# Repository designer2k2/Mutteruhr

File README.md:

# Mutteruhr
a pulse of alternating polarity every minute.

Motherclock, or german "Mutteruhr" is a arduino based Master Clock or german "Hauptuhr". 
It generates a short pulse of alternating polarity to drive so called slave clocks or german "Nebenuhr".

https://en.wikipedia.org/wiki/Master_clock

With a DC/DC converter it uses minimal power, the highly accurate DS3231 RTC to keep time, and a Arduino Nano Every as a Brain.

## Circuit

Schematic: https://github.com/designer2k2/Mutteruhr/blob/main/MotherClock/Motherclock%20Schematic.pdf

The actual clock drive is a transistor h-bridge, parts can be either SMD or THT. 

2 Buttons and a DIL switch is on it to make settings while the clock operates.

A small mosfet can be used to switch some LED´s on/off

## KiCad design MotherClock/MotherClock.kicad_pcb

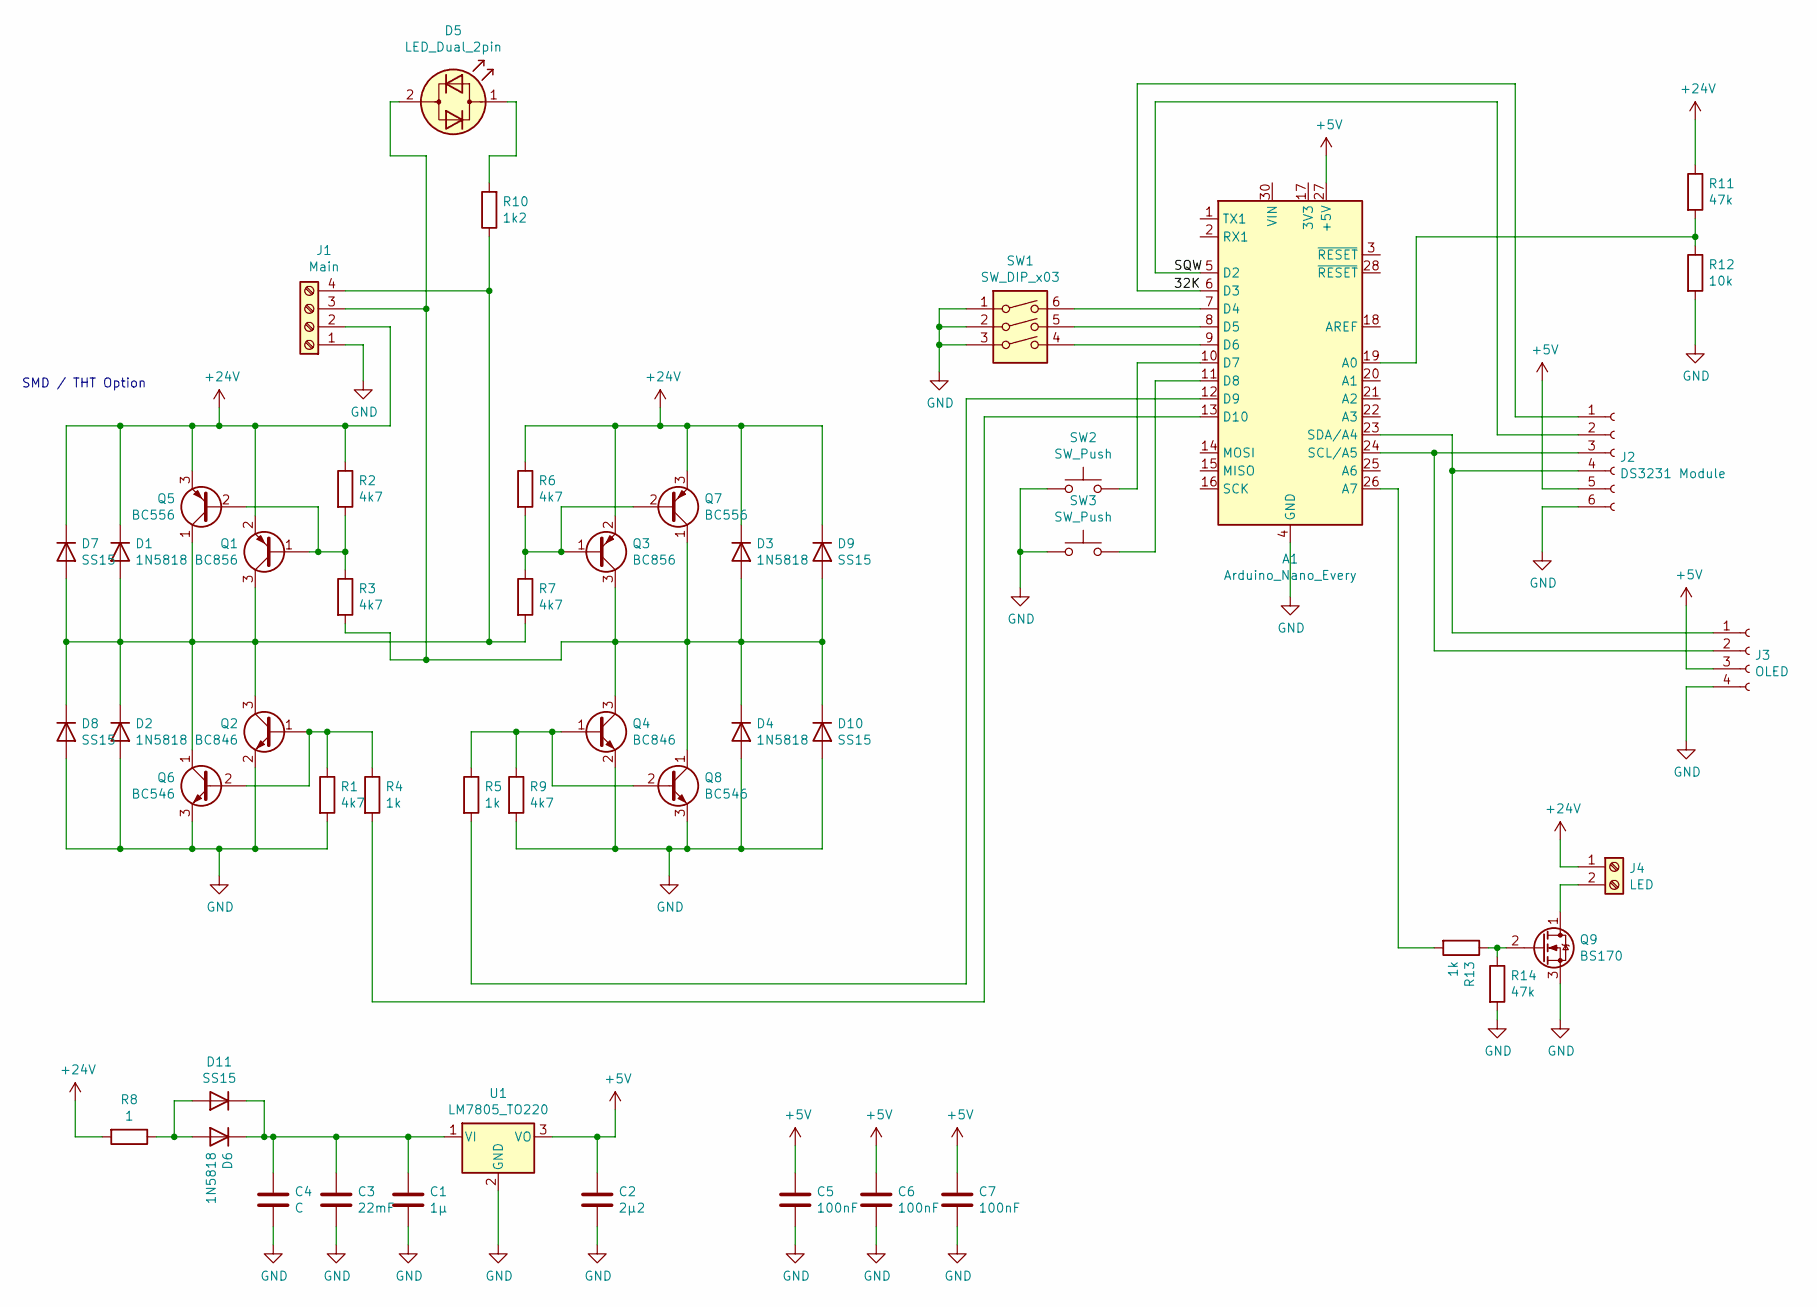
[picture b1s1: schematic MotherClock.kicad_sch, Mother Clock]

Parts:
A1: Arduino_Nano_Every; Arduino_Nano
C1: 1µ; CP_Radial_D5.0mm_P2.00mm
C2: 2µ2; CP_Radial_D5.0mm_P2.00mm
C3: 22mF; CP_Radial_D35.0mm_P10.00mm_SnapIn
C4: C; CP_Radial_D18.0mm_P7.50mm
C5, C6, C7: 100nF; C_0805_2012Metric
D1, D2, D3, D4, D6: 1N5818; D_DO-41_SOD81_P10.16mm_Horizontal
D5: LED_Dual_2pin; LED_D3.0mm_Clear
D7, D8, D9, D10, D11: SS15; D_SMA
J1: Main; TerminalBlock_Altech_AK300-4_P5.00mm
J2: DS3231 Module; PinHeader_1x06_P2.54mm_Vertical
J3: OLED; PinHeader_1x04_P2.54mm_Vertical
J4: LED; TerminalBlock_Altech_AK300-2_P5.00mm
Q1, Q3: BC856; SOT-23
Q2, Q4: BC846; SOT-23
Q5, Q7: BC556; TO-92_Inline_Wide
Q6, Q8: BC546; TO-92_Inline_Wide
Q9: BS170; TO-92_Inline
R1, R2, R3, R6, R7, R9: 4k7; R_1206_3216Metric
R4, R5, R13: 1k; R_1206_3216Metric
R8: 1; R_1206_3216Metric
R10: 1k2; R_1206_3216Metric
R11, R14: 47k; R_1206_3216Metric
R12: 10k; R_1206_3216Metric
SW1: SW_DIP_x03; SW_DIP_SPSTx03_Slide_9.78x9.8mm_W7.62mm_P2.54mm
SW2, SW3: SW_Push; SW_PUSH_6mm_H5mm
U1: LM7805_TO220; TO-220-3_Vertical

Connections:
+5V: A1.27 (+5V), C2.1, C5.1, C6.1, C7.1, J2.5, J3.3, U1.3 (VO)
+24V: D1.1 (K), D3.1 (K), D7.1 (K), D9.1 (K), J1.2, J4.1, Q1.2 (E), Q3.2 (E), Q5.3 (E), Q7.3 (E), R2.1, R6.1, R8.2, R11.1
GND: A1.4 (GND), A1.29 (GND), C1.2, C2.2, C3.2, C4.2, C5.2, C6.2, C7.2, D2.2 (A), D4.2 (A), D8.2 (A), D10.2 (A), J1.1, J2.6, J3.4, Q2.2 (E), Q4.2 (E), Q6.3 (E), Q8.3 (E), Q9.3 (S), R1.2, R9.2, R12.2, R14.2, SW1.1, SW1.2, SW1.3, SW2.1, SW3.1, U1.2 (GND)
unnamed: A1.5 (D2), J2.2
unnamed: A1.6 (D3), J2.1
unnamed: A1.7 (D4), SW1.6
unnamed: A1.8 (D5), SW1.5
unnamed: A1.9 (D6), SW1.4
unnamed: A1.10 (D7), SW2.2
unnamed: A1.11 (D8), SW3.2
unnamed: A1.12 (D9), R5.2
unnamed: A1.13 (D10), R4.2
unnamed: A1.19 (A0), R11.2, R12.1
unnamed: A1.23 (SDA/A4), J2.4, J3.1
unnamed: A1.24 (SCL/A5), J2.3, J3.2
unnamed: A1.26 (A7), R13.2
unnamed: C1.1, C3.1, C4.1, D6.1 (K), D11.1 (K), U1.1 (VI)
unnamed: D1.2 (A), D2.1 (K), D7.2 (A), D8.1 (K), J1.4, Q1.3 (C), Q2.3 (C), Q5.1 (C), Q6.1 (C), R7.2, R10.1
unnamed: D5.1 (KA), R10.2
unnamed: D3.2 (A), D4.1 (K), D5.2 (AK), D9.2 (A), D10.1 (K), J1.3, Q3.3 (C), Q4.3 (C), Q7.1 (C), Q8.1 (C), R3.2
unnamed: D6.2 (A), D11.2 (A), R8.1
unnamed: J4.2, Q9.1 (D)
unnamed: Q1.1 (B), Q5.2 (B), R2.2, R3.1
unnamed: Q2.1 (B), Q6.2 (B), R1.1, R4.1
unnamed: Q3.1 (B), Q7.2 (B), R6.2, R7.1
unnamed: Q4.1 (B), Q8.2 (B), R5.1, R9.1
unnamed: Q9.2 (G), R13.1, R14.1

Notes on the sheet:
SMD / THT Option

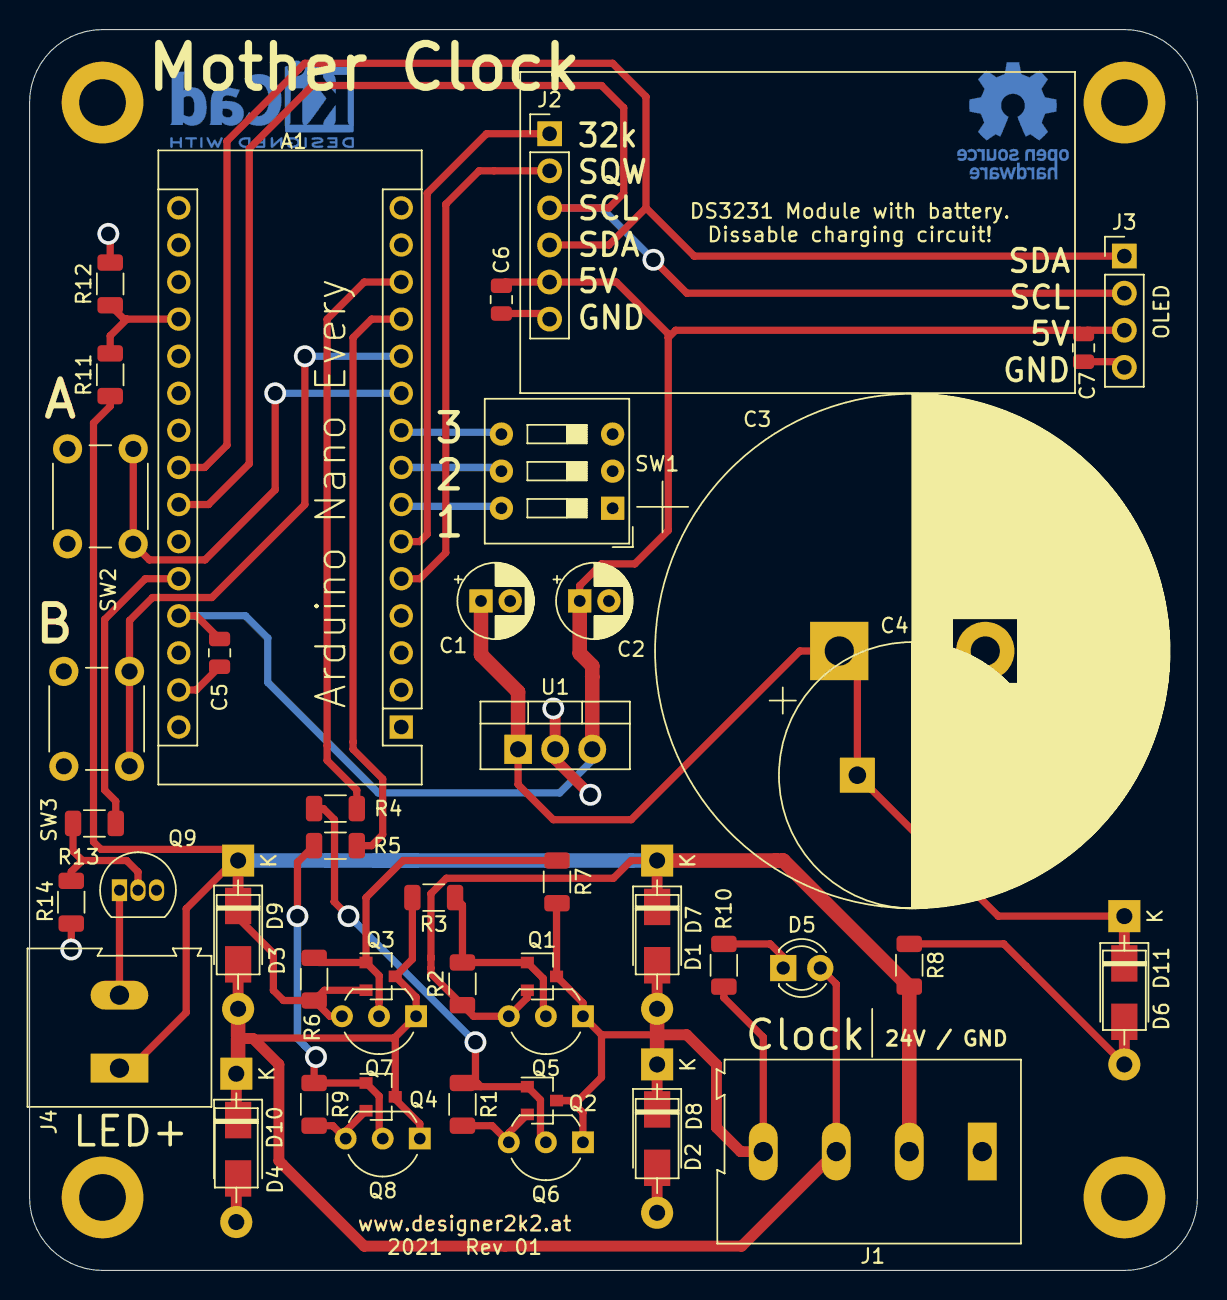
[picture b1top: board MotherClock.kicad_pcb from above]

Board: 2 copper layers, 80.0 x 85.0 mm, 50 parts (0 on the bottom side), 27 nets.

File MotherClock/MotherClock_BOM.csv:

Comment,Designator,Footprint,LCSC
"Arduino_Nano_Every","A1","Module:Arduino_Nano",""
"1µ","C1","Capacitor_THT:CP_Radial_D5.0mm_P2.00mm",""
"2µ2","C2","Capacitor_THT:CP_Radial_D5.0mm_P2.00mm",""
"22mF","C3","Capacitor_THT:CP_Radial_D35.0mm_P10.00mm_SnapIn",""
"C","C4","Capacitor_THT:CP_Radial_D18.0mm_P7.50mm",""
"100nF","C5,C6,C7","Capacitor_SMD:C_0805_2012Metric",""
"1N5818 ","D1,D2,D3,D4,D6","Diode_THT:D_DO-41_SOD81_P10.16mm_Horizontal",""
"LED_Dual_2pin","D5","LED_THT:LED_D3.0mm_Clear",""
"SS15","D7,D8,D9,D10,D11","Diode_SMD:D_SMA",""
"Main","J1","TerminalBlock:TerminalBlock_Altech_AK300-4_P5.00mm",""
"DS3231 Module","J2","Connector_PinHeader_2.54mm:PinHeader_1x06_P2.54mm_Vertical",""
"OLED","J3","Connector_PinHeader_2.54mm:PinHeader_1x04_P2.54mm_Vertical",""
"LED","J4","TerminalBlock:TerminalBlock_Altech_AK300-2_P5.00mm",""
"BC856","Q1,Q3","Package_TO_SOT_SMD:SOT-23",""
"BC846","Q2,Q4","Package_TO_SOT_SMD:SOT-23",""
"BC556","Q5,Q7","Package_TO_SOT_THT:TO-92_Inline_Wide",""
"BC546","Q6,Q8","Package_TO_SOT_THT:TO-92_Inline_Wide",""
"BS170","Q9","Package_TO_SOT_THT:TO-92_Inline",""
"1k2","R10","Resistor_SMD:R_1206_3216Metric",""
"47k","R11,R14","Resistor_SMD:R_1206_3216Metric",""
"10k","R12","Resistor_SMD:R_1206_3216Metric",""
"4k7","R1,R2,R6,R9","Resistor_SMD:R_1206_3216Metric",""
"2k2","R3,R7","Resistor_SMD:R_1206_3216Metric",""
"1k","R4,R5,R13","Resistor_SMD:R_1206_3216Metric",""
"1","R8","Resistor_SMD:R_1206_3216Metric",""
"SW_DIP_x03","SW1","Button_Switch_THT:SW_DIP_SPSTx03_Slide_9.78x9.8mm_W7.62mm_P2.54mm",""
"SW_Push","SW2,SW3","Button_Switch_THT:SW_PUSH_6mm_H5mm",""
"LM7805_TO220","U1","Package_TO_SOT_THT:TO-220-3_Vertical",""

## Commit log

2021-12-07 Initial fill
    PCB and software are usable
2022-06-15 Bugfix with name clock conflict
2022-07-03 Update PCB to KiCad 6
2022-07-08 begin work on additional method to run
2022-07-08 working update
    DIP 1 now selects between interrupts or not (looking for a strange bug that stops the clock after some weeks)
2022-07-09 add i2c scanner and improve lcd readability
2023-01-06 latest changes
    * begin work on additional method to run
    * working update
    DIP 1 now selects between interrupts or not (looking for a strange bug that stops the clock after some weeks)
    * add i2c scanner and improve lcd readability
    * Create spell-check.yml
    * Create compile-sketch.yml
